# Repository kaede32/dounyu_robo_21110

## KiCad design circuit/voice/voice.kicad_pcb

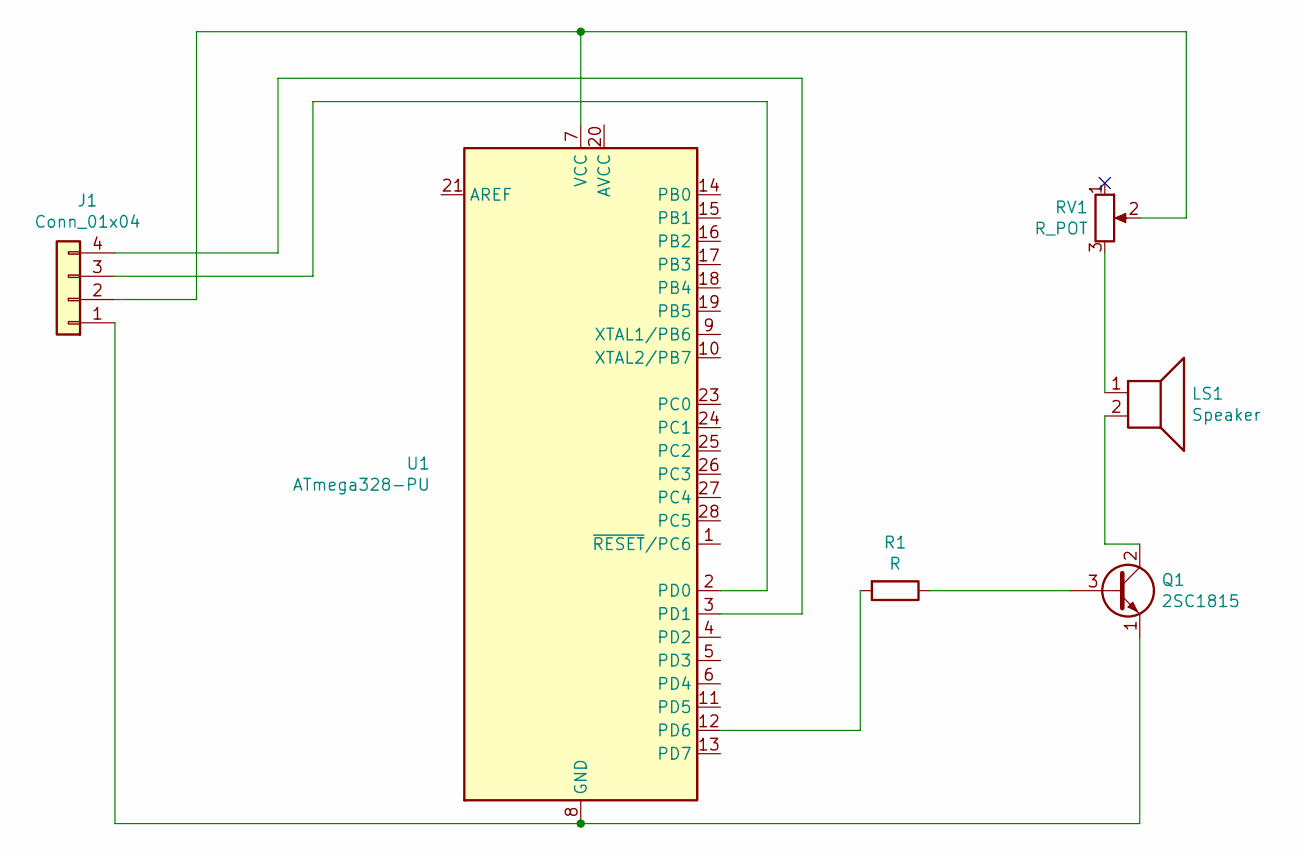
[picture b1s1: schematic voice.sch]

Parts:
J1: Conn_01x04; PinHeader_1x04_P2.54mm_Vertical
LS1: Speaker; PinHeader_1x02_P2.00mm_Vertical
Q1: 2SC1815; TO-92_Inline_Wide
R1: R; R_Axial_DIN0207_L6.3mm_D2.5mm_P10.16mm_Horizontal
RV1: R_POT; Potentiometer_Bourns_3386P_Vertical
U1: ATmega328-PU; DIP-28_W7.62mm

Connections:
unnamed: J1.1, Q1.1 (E), U1.8 (GND), U1.22 (GND)
unnamed: J1.2, RV1.2, U1.7 (VCC)
unnamed: J1.3, U1.2 (PD0)
unnamed: J1.4, U1.3 (PD1)
unnamed: LS1.1, RV1.3
unnamed: LS1.2, Q1.2 (C)
unnamed: Q1.3 (B), R1.1
unnamed: R1.2, U1.12 (PD6)

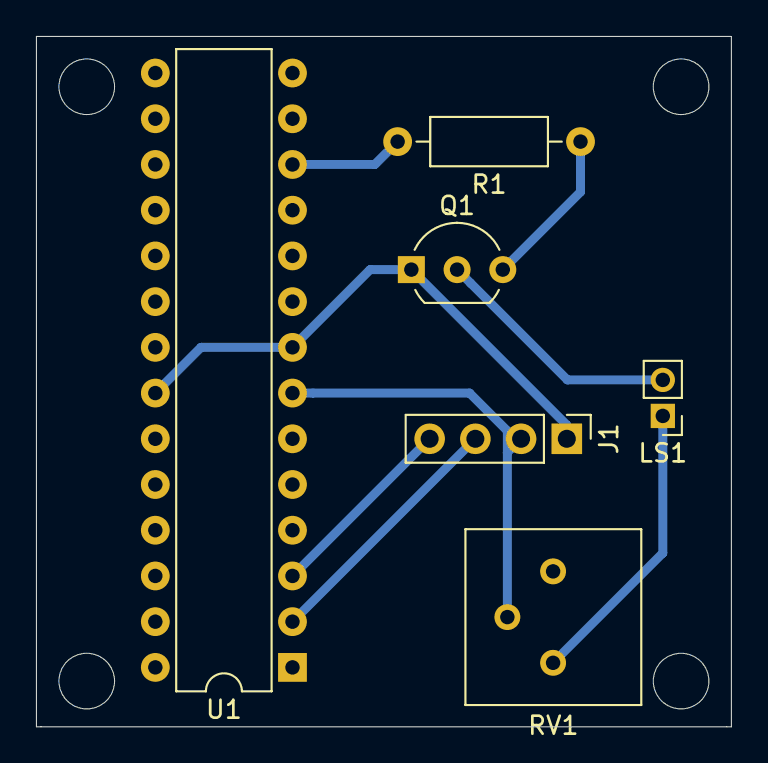
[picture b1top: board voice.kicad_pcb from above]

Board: 2 copper layers, 38.6 x 38.4 mm, 6 parts (0 on the bottom side), 8 nets.

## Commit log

2021-05-12 ”基板作成 はんだ付け”
